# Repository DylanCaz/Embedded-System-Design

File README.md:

# Embedded-System-Design
This repository contains projects that were 
created for my universities Embeded System 
Design course

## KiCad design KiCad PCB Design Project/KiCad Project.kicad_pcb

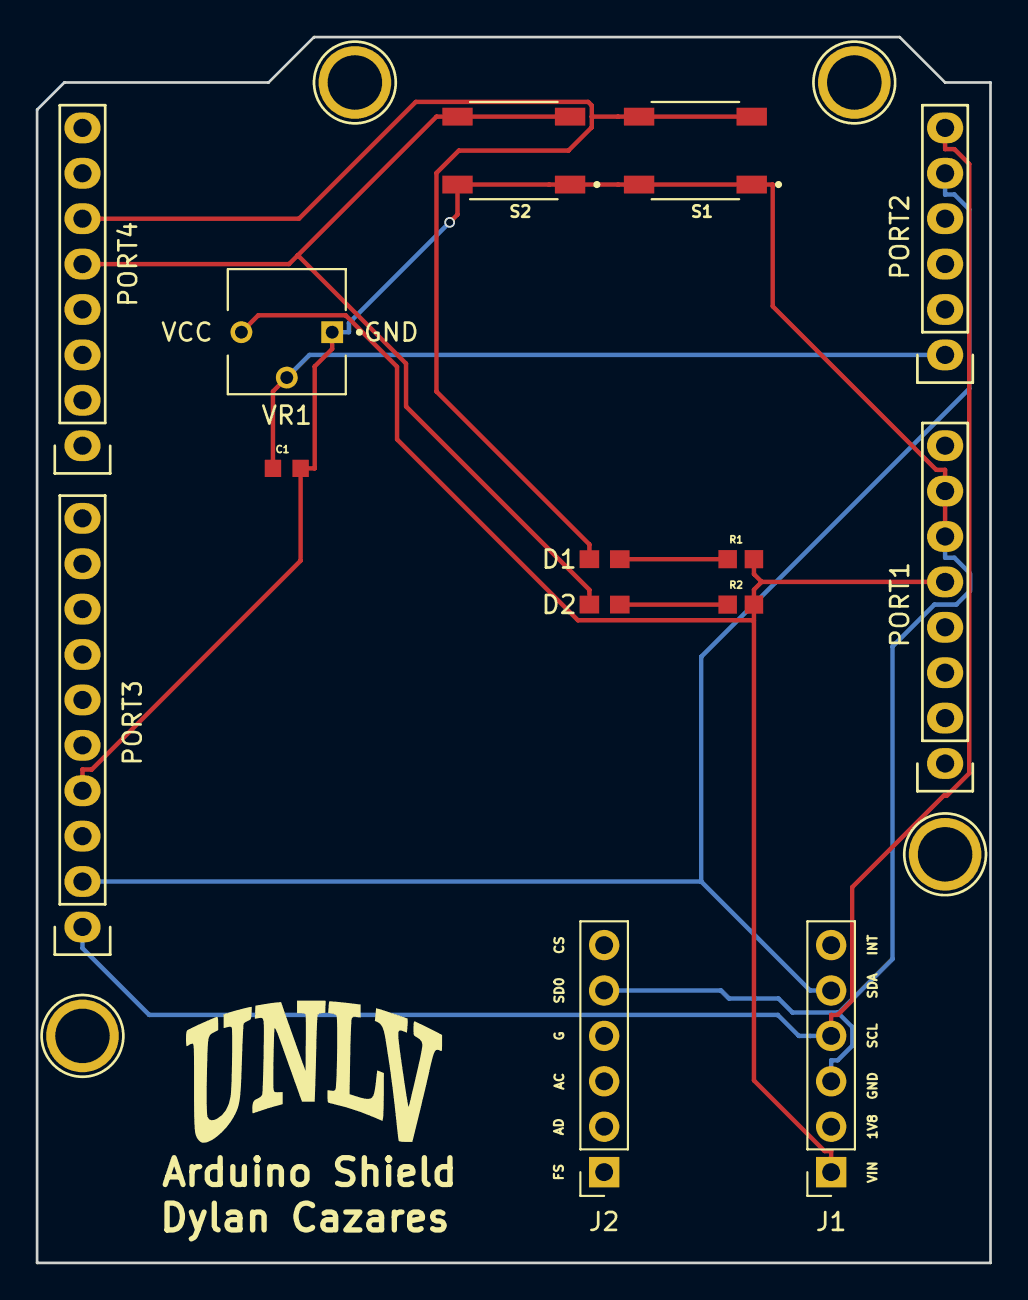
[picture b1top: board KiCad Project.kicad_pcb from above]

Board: 2 copper layers, 53.3 x 68.6 mm, 18 parts (0 on the bottom side), 9 nets.

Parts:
C1: 0.1uF; CAPC1608X90N
D1, D2: LTST-C193TGKT-5A; 0603
J1, J2: Conn_01x06_Female; PinSocket_1x06_P2.54mm_Vertical
P5, P6, P7, P8: CONN_01X01; Arduino_1pin
PORT1: Power; Socket_Strip_Arduino_1x08
PORT2: Analog; Socket_Strip_Arduino_1x06
PORT3: Digital; Socket_Strip_Arduino_1x10
PORT4: Digital; Socket_Strip_Arduino_1x08
R1, R2: RC0603JR-071KL; RESC1607X60N
S1, S2: 8-1437565-1; SW_8-1437565-1
VR1: 3362P-1-103LF; TRIM_3362P-1-103LF

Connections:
+5V: J1.1, PORT1.5, R1.2, R2.2, VR1.3
/2: D1.1, PORT4.6, S1.3, S1.4
/3(**): D2.1, PORT4.5, S2.3, S2.4
/A0: C1.1, PORT2.1, VR1.2
/A4(SDA): J1.5, PORT2.5, PORT3.2
/A5(SCL): J1.4, PORT2.6, PORT3.1
GND: C1.2, J1.3, J2.5, PORT1.6, PORT1.7, PORT3.4, S1.1, S1.2, S2.1, S2.2, VR1.1
unnamed: D1.2, R1.1
unnamed: D2.2, R2.1
